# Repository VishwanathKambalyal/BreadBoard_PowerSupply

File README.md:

# Breadboard Power Supply Module

This project is a **breadboard power supply module** that takes an input voltage of **6-12V**, steps it down to **5V or 3.3V** (selectable via a jumper), and distributes the chosen voltage to the horizontal power rails of a breadboard.

### ⚠ Note:
The distance between horizontal pins may vary depending on the breadboard brand, so please check compatibility before use.

## Features
- **Input Voltage:** 6V - 12V  
- **Output Voltage:** Selectable 5V / 3.3V  
- **Voltage Regulation:** Provides stable power output  
- **Breadboard Compatibility:** Designed to fit standard breadboards, but compatibility may vary  

## Project Images

### Schematic  

### Front Layer  

### Back Layer  

### Mixed View  

## 3D View  

### Bottom View  

### Side View  

### Complete PCB View  

## How to Use  
1. Connect an external power source (6V - 12V DC).  
2. Use the jumper to select the output voltage (5V or 3.3V).  
3. Plug the module into a breadboard, ensuring proper alignment.  
4. The selected voltage will be distributed to the horizontal power rails.  

## License  
This project is open-source. Feel free to modify and improve it!

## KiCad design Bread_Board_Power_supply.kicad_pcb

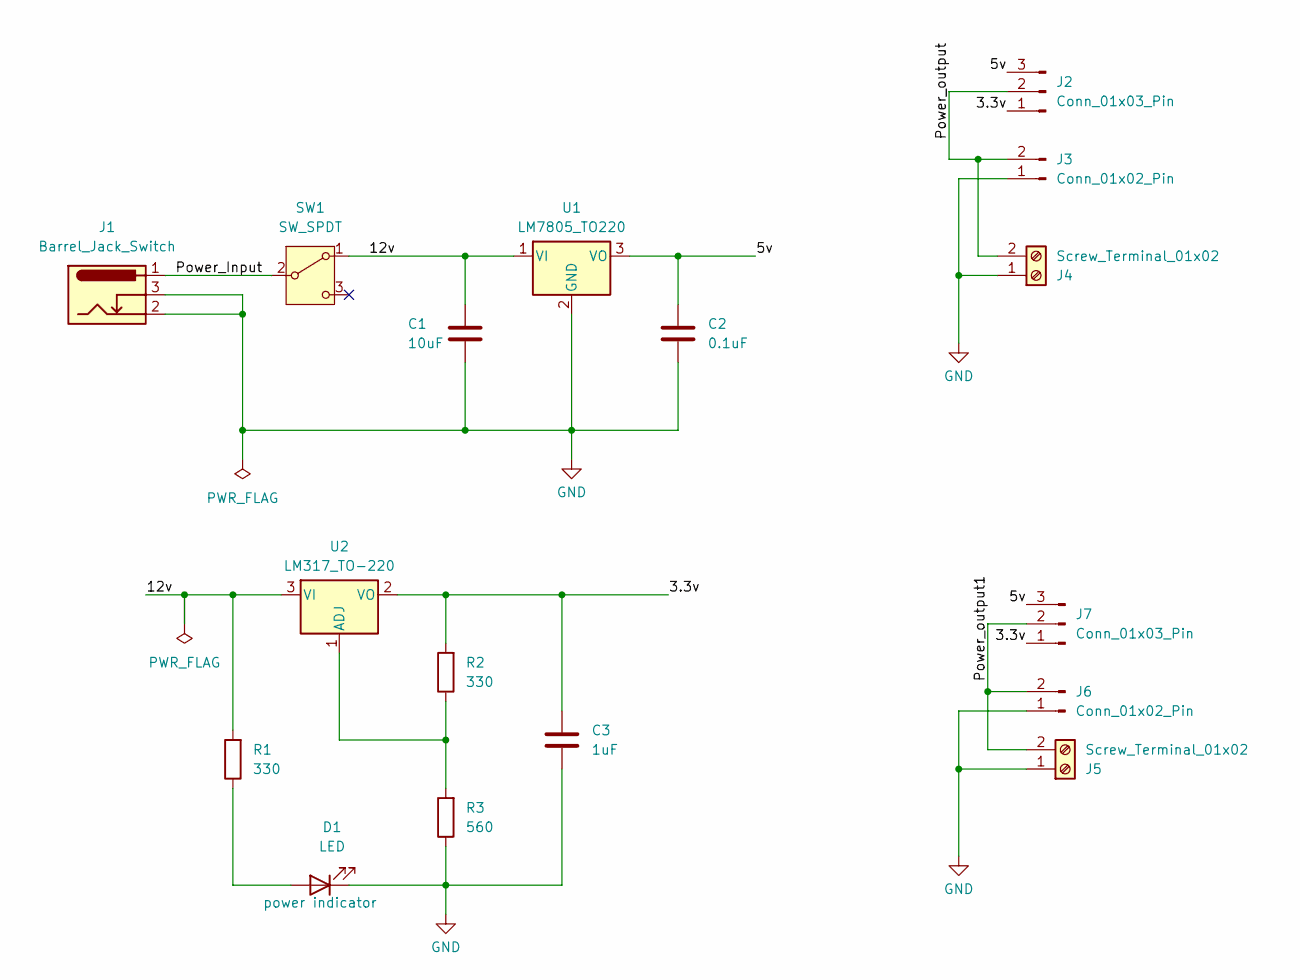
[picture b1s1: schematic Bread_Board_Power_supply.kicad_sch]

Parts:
C1: 10uF; C_Radial_D5.0mm_H7.0mm_P2.00mm
C2: 0.1uF; C_1206_3216Metric
C3: 1uF; C_0805_2012Metric
D1: LED; LED_1206_3216Metric
J1: Barrel_Jack_Switch; BarrelJack_Horizontal
J2, J7: Conn_01x03_Pin; PinHeader_1x03_P2.54mm_Vertical
J3, J6: Conn_01x02_Pin; PinHeader_1x02_P2.54mm_Vertical
J4, J5: Screw_Terminal_01x02; TerminalBlock_Phoenix_MKDS-1,5-2-5.08_1x02_P5.08mm_Horizont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
R1, R2: 330; R_Axial_DIN0204_L3.6mm_D1.6mm_P5.08mm_Horizontal
R3: 560; R_Axial_DIN0204_L3.6mm_D1.6mm_P5.08mm_Horizontal
SW1: SW_SPDT; SW_Slide-03_Wuerth-WS-SLTV_10x2.5x6.4_P2.54mm
U1: LM7805_TO220; TO-220-3_Vertical
U2: LM317_TO-220; TO-220-3_Vertical

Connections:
/3.3v: C3.2, J2.1, J7.1, R2.2, U2.2 (VO)
/5v: C2.2, J2.3, J7.3, U1.3 (VO)
/12v: C1.2, R1.2, SW1.1 (A), U1.1 (VI), U2.3 (VI)
/Power_Input: J1.1, SW1.2 (B)
/Power_output: J2.2, J3.2, J4.2
/Power_output1: J5.2, J6.2, J7.2
GND: C1.1, C2.1, C3.1, D1.1 (K), J1.2, J1.3, J3.1, J4.1, J5.1, J6.1, R3.1, U1.2 (GND)
unnamed: D1.2 (A), R1.1
unnamed: R2.1, R3.2, U2.1 (ADJ)

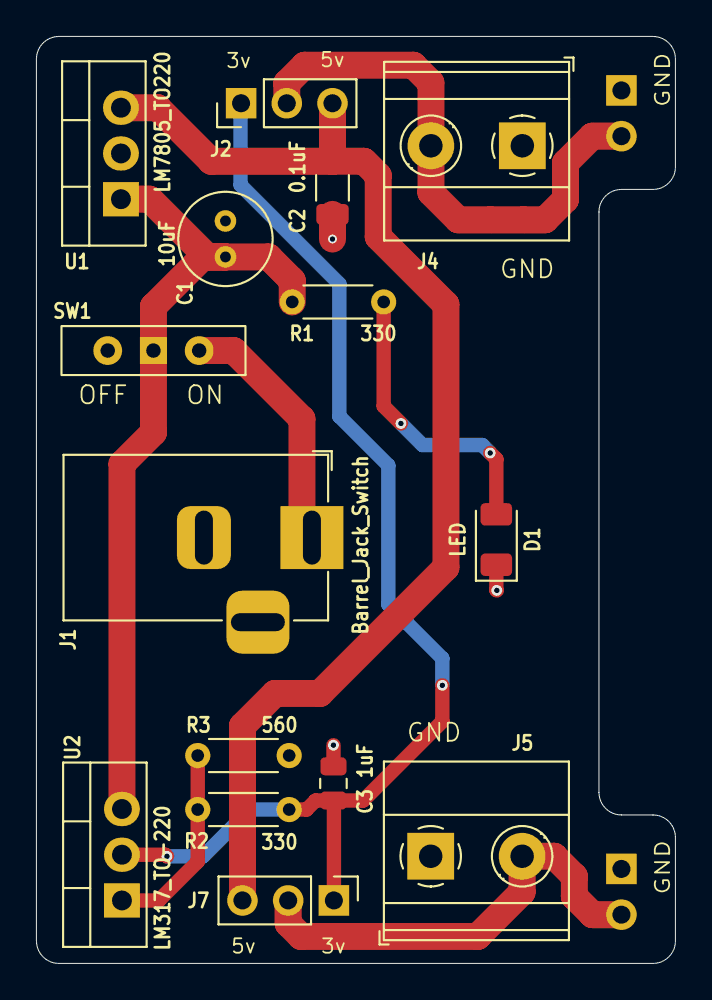
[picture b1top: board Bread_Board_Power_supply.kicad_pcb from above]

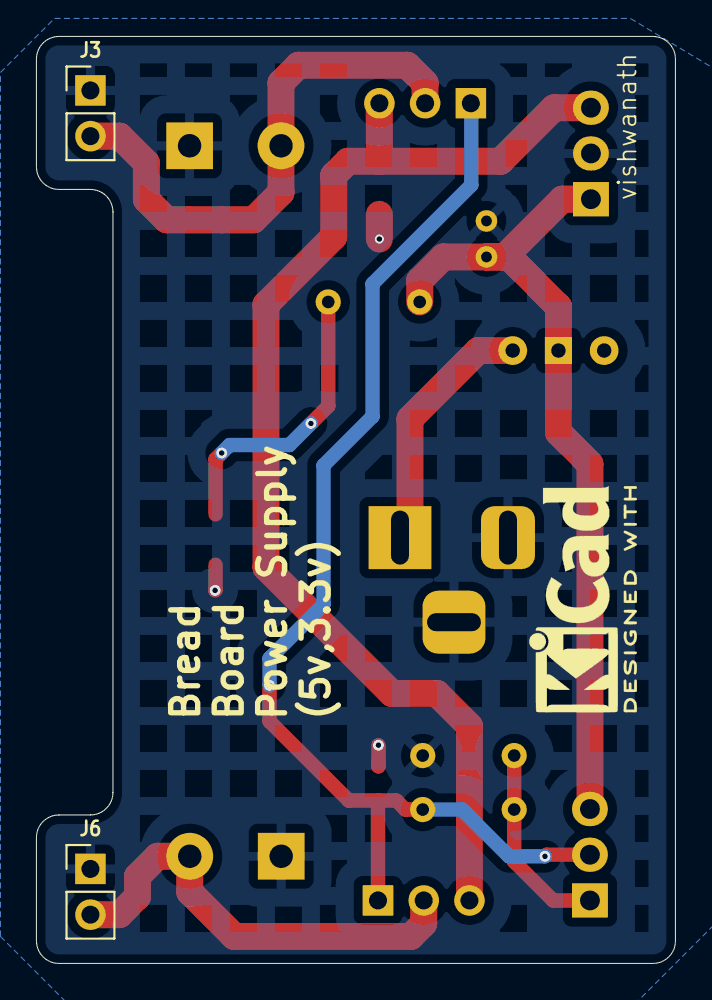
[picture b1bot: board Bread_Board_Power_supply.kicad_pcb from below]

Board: 2 copper layers, 35.5 x 51.5 mm, 17 parts (2 on the bottom side), 9 nets.

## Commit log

2025-02-20 Initial commit - PCB design project
